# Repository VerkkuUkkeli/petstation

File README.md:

# petstation
Web server for the pet station

### Quickstart
1. Pull code from github repo using the command ```git clone https://github.com/VerkkuUkkeli/petstation```
1. ```cd petstation```
1. Use the command ```python3 main.py``` to start the server
1. Connect to the server by typing ```localhost:5000``` to the address field of a web browser.

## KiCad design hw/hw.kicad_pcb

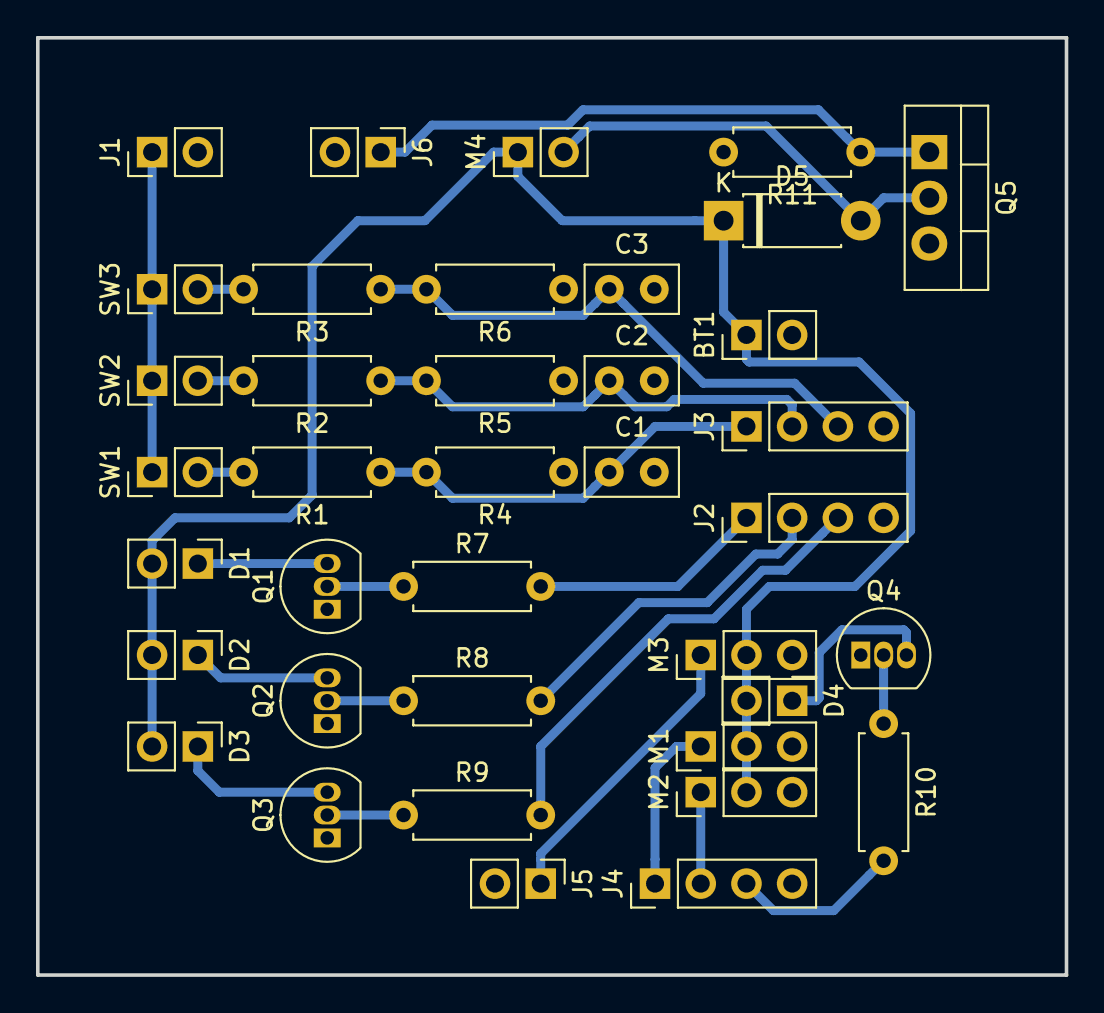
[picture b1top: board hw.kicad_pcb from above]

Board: 2 copper layers, 57.1 x 52.1 mm, 38 parts (0 on the bottom side), 26 nets.

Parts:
BT1: Battery; PinHeader_1x02_P2.54mm_Vertical
C1, C2, C3: 100n; C_Disc_D5.0mm_W2.5mm_P2.50mm
D1, D2, D3: LED; PinHeader_1x02_P2.54mm_Vertical
D4: LASER; PinHeader_1x02_P2.54mm_Vertical
D5: 1N4001; D_DO-41_SOD81_P7.62mm_Horizontal
J1: Pi Operating Voltage; PinHeader_1x02_P2.54mm_Vertical
J2: Pi LED Signals In; PinHeader_1x04_P2.54mm_Vertical
J3: Pi Button Signals Out; PinHeader_1x04_P2.54mm_Vertical
J4: Laser Turret Signals In; PinHeader_1x04_P2.54mm_Vertical
J5: Mouse Servo Signal In; PinHeader_1x02_P2.54mm_Vertical
J6: Fan Signal In; PinHeader_1x02_P2.54mm_Vertical
M1: Yaw; PinHeader_1x03_P2.54mm_Vertical
M2: Pitch; PinHeader_1x03_P2.54mm_Vertical
M3: Mouse; PinHeader_1x03_P2.54mm_Vertical
M4: Fan; PinHeader_1x02_P2.54mm_Vertical
Q1, Q2, Q3, Q4: 2N3904; TO-92_Inline
Q5: IRLZ44N; TO-220-3_Vertical
R1, R2, R3, R7, R8, R9, R10: 1k; R_Axial_DIN0207_L6.3mm_D2.5mm_P7.62mm_Horizontal
R4, R5, R6, R11: 10k; R_Axial_DIN0207_L6.3mm_D2.5mm_P7.62mm_Horizontal
SW1, SW2, SW3: SW_Push; PinHeader_1x02_P2.54mm_Vertical

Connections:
+3V3: J1.1, SW1.1, SW2.1, SW3.1
+5V: BT1.1, D1.2, D2.2, D3.2, D4.2, D5.1, M1.2, M2.2, M3.2, M4.1
GND: BT1.2, C1.2, C2.2, C3.2, J1.2, J2.4, J3.4, J4.4, J5.2, J6.2, M1.3, M2.3, M3.3, Q1.1, Q2.1, Q3.1, Q4.1, Q5.3, R4.1, R5.1, R6.1, R11.2
unnamed: C1.1, J3.1, R1.1, R4.2
unnamed: C2.1, J3.2, R2.1, R5.2
unnamed: C3.1, J3.3, R3.1, R6.2
unnamed: D1.1, Q1.3
unnamed: D2.1, Q2.3
unnamed: D3.1, Q3.3
unnamed: D4.1, Q4.3
unnamed: D5.2, M4.2, Q5.2
unnamed: J2.1, R7.2
unnamed: J2.2, R8.2
unnamed: J2.3, R9.2
unnamed: J4.1, M1.1
unnamed: J4.2, M2.1
unnamed: J4.3, R10.2
unnamed: J5.1, M3.1
unnamed: J6.1, Q5.1, R11.1
unnamed: Q1.2, R7.1
unnamed: Q2.2, R8.1
unnamed: Q3.2, R9.1
unnamed: Q4.2, R10.1
unnamed: R1.2, SW1.2
unnamed: R2.2, SW2.2
unnamed: R3.2, SW3.2

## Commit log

2018-11-07 Working hello world flask app
2018-11-07 Added html template and javascript for index page
2018-11-07 Added client side key event detection. Added sending keyevents using XMLHttpRequests from client to server. Added handlers to keyevent XMLHttpRequests to backend
2018-11-07 Added support for client laser control requests
2018-11-07 Added suport for playing audio on the server through the web interface
2018-11-07 Changed audio playback to use XMLHttpRequest instead of form submission (get request with query parameters), which prevents page refresh when audio is played. Minor template UI changes
2018-11-07 removed unused imports
2018-11-12 Added hardware support for servo control
2018-11-12 Added hardware support for controlling the laser module
2018-11-14 Added support for video streaming
2018-11-14 Added css files for html templates
2018-11-17 Created petstation circuit schematic
2018-11-17 Created pcb layout
2018-11-18 Added pinout diagram for pcb
2018-11-18 Added software support for button presses
2018-11-18 Added button handlers for driving button LEDs
2018-11-19 Added CSS styling
2018-11-19 Fixed bugs introduced by Vilis
2018-11-19 Fixed CSS formatting on camera page
2018-11-19 Added support for mouse waggling
2018-11-19 Adjusted mouse servo range
